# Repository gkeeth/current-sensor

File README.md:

# current-sensor
Hall effect current sensor board. Invasive (connected in series with DUT), with BNC output to oscilloscope.

Designed to fit in Hammond 1593W enclosure. Powered by 9V battery. Includes PCBs for front and back panels (20A and 36A options for front panel).

## Specifications:
- Output: 0-5V, DC-coupled
- Maximum input current: +/-20A. Different current limits are possible by
selecting a different version of the ACS730 Hall effect IC (also changes sensitivity)
  - ACS730xxxxx-20AB: +/- 20A
  - ACS730xxxxx-40AB: +/- 40A [limited to 36A by binding posts]
- Gain: selectable between x1, x10, and x100
  - -20AB: x1 (100mV/A), x10 (1V/A), and x100 (10V/A)
  - -40AB: x1 (50mV/A), x10 (500mV/A), and x100 (5V/A)
- Bandwidth: selectable between 1kHz, 10kHz, and 100kHz
- Power supply: 9V battery

## Adjustment Procedure:
The only adjustment needed is to adjust the zero-current offset voltage so that
the output reads zero when zero current is applied to the input.

1. Disconnect wires from input jacks so that input current is zero.
2. Set Gain to 1x and Bandwidth to 1kHz.
3. Adjust trimmer RV1 until the voltage at the output (between BNC center pin
and shell) is as close to 0V as possible.
4. Increase gain to 10x/100x and fine-tune adjustment.

## Possible Future Improvements:
- use a multi-turn trimpot for zero-current offset adjustment
- make adjustment trimpot available at rear panel for trim without removing case

## Schematic:
[PDF of schematic](pdf/current-sensor.pdf)

## Layout:

## BOM:
[BOM for main board](bom/current-sensor.csv)

### Additional components:
Note that the board was designed with Molex SL crimp terminals for the LED and 9V battery,
but those connections could be done with another crimp family or even soldered. Substitute
connectors as appropriate.

| Quantity | Manufacturer | Manufacturer PN  | Distributor | Distributor PN | Notes                |
| -------- | ------------ | ---------------- | ----------- | -------------- | -------------------- |
| 1        | Hammond      | 1593WBK          | Digikey     | 164-1593WBK-ND | case                 |
| 1        | Hammond      | 1593ATS50        | Digikey     | HM1442-ND      | PCB mounting screws  |
| 1        | MPD          | BH9VW            | Digikey     | BH9VW-ND       | battery holder       |
| 2        | Cal Test     | CT2232-4         | Digikey     | BKCT2232-4-ND  | binding posts        |
| 1        | C&K          | G003G            | Digikey     | 401-1205-ND    | power button cap     |
| 1        | Lumex        | SSI-LXH312ID-150 | Digikey     | 67-1190-ND     | power LED            |
| 2        | Molex        | 0190050010       | Digikey     | WM18241-ND     | QC connectors        |
| 4        | Molex        | 0016020097       | Digikey     | WM2513-ND      | SL crimp terminals for LED and battery |
| 2        | Molex        | 0050579402       | Digikey     | WM2900-ND      | SL crimp housings for LED and battery  |

## Front/Rear Panel and Assembly:

## License:
Licensed under the [Creative Commons Attribution-ShareAlike 4.0 International License][cc-by-sa].

[![CC BY-SA 4.0][cc-by-sa-image]][cc-by-sa]

[cc-by-sa]: http://creativecommons.org/licenses/by-sa/4.0/
[cc-by-sa-image]: https://licensebuttons.net/l/by-sa/4.0/88x31.png

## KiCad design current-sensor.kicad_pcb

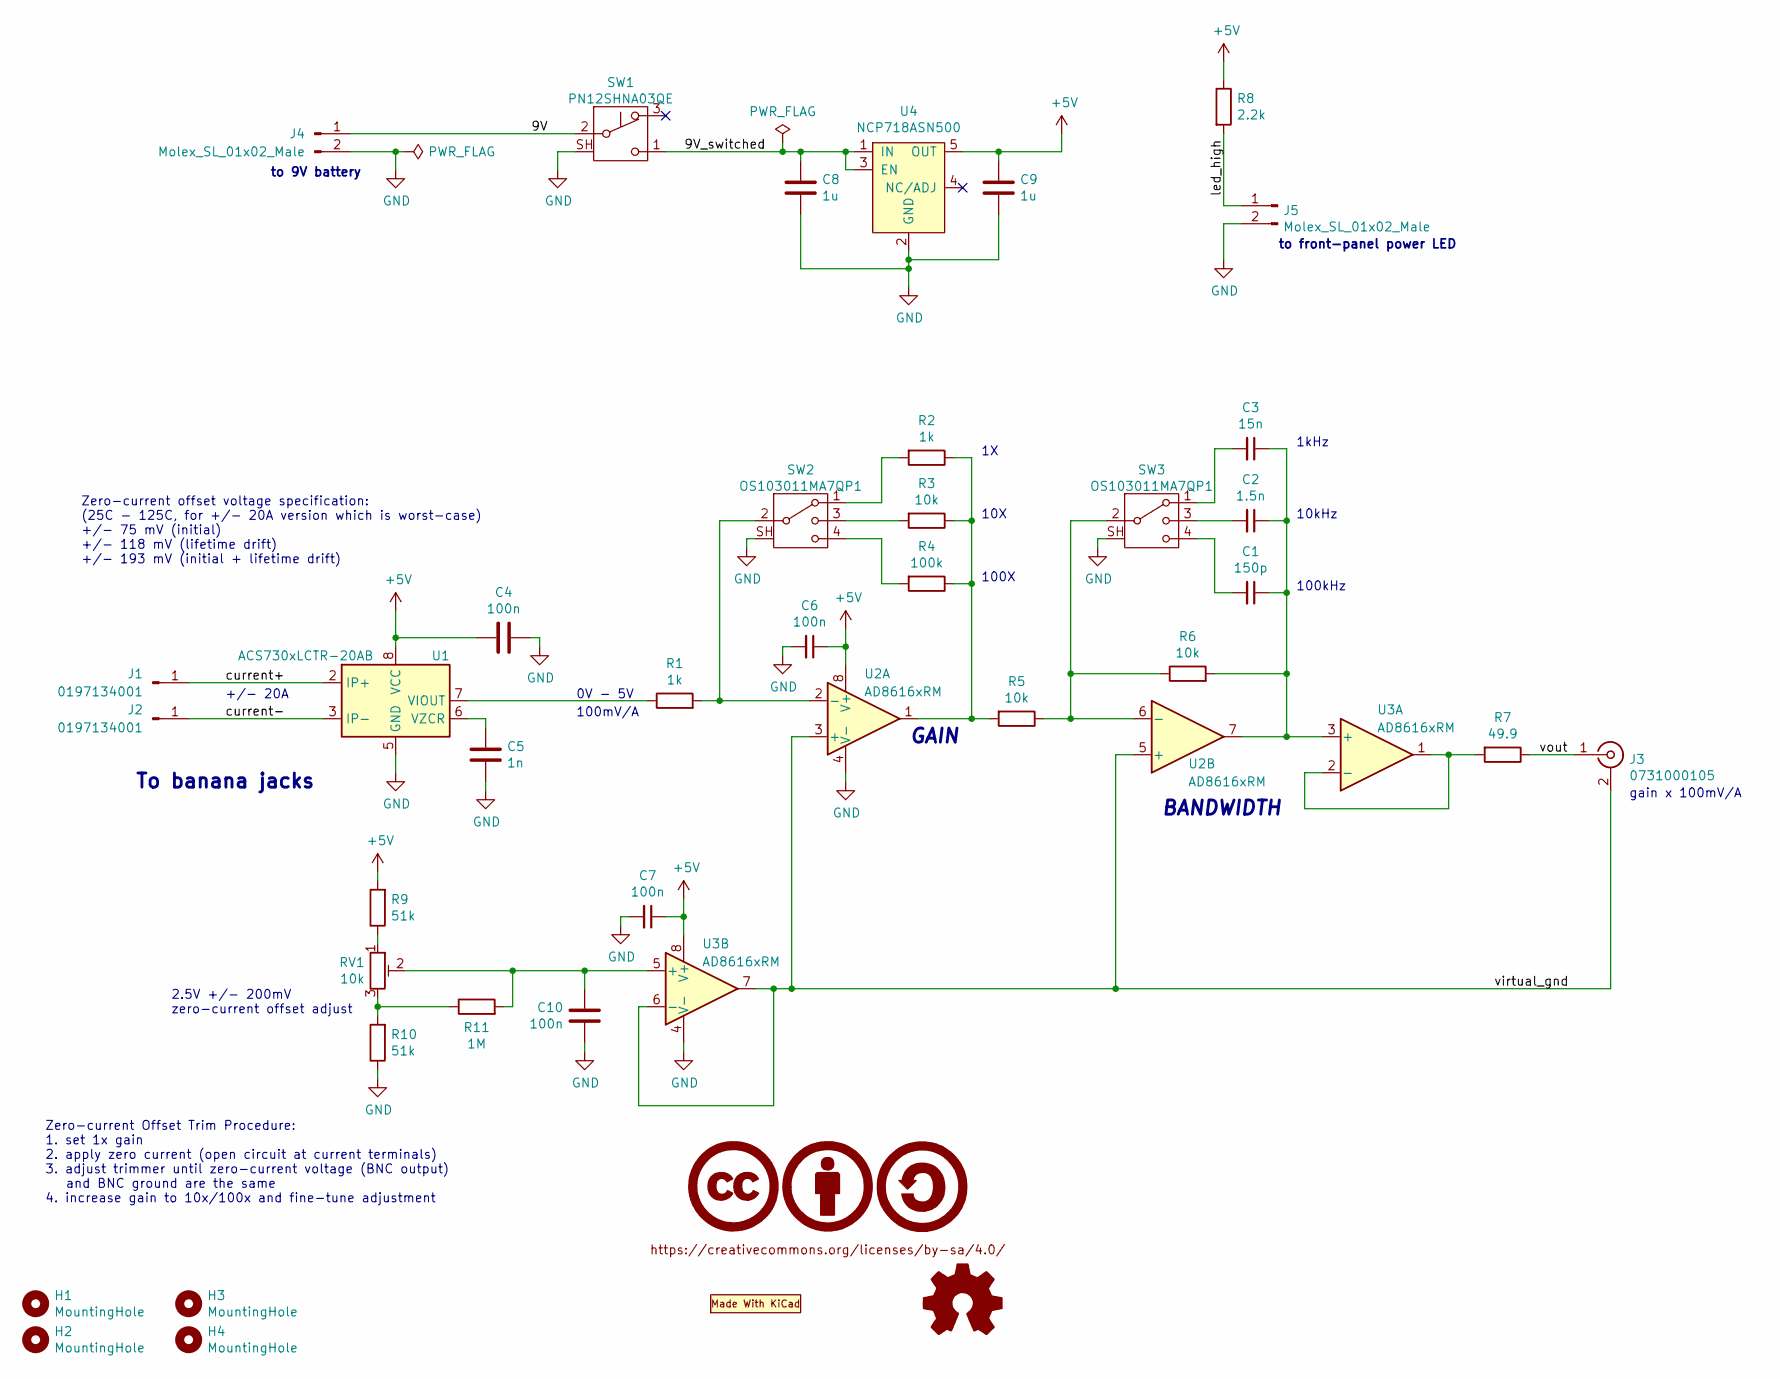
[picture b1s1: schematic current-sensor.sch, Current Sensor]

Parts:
C1: 150p; C_0603_1608Metric
C2: 1.5n; C_0603_1608Metric
C3: 15n; C_0603_1608Metric
C4, C6, C7, C10: 100n; C_0603_1608Metric
C5: 1n; C_0603_1608Metric
C8, C9: 1u; C_0805_2012Metric
H1, H2, H3, H4: MountingHole; MountingHole_3.2mm_M3
J1, J2: ‎0197134001‎; Connector_Molex_Quixon_19713-4001_1x01_Horizontal; Manufacturer PN 0197134001
J3: 0731000105; BNC_Molex_73100-0105_Horizontal; Manufacturer PN 0731000105
J4, J5: Molex_SL_01x02_Male; Molex_SL_A-70543-0001_1x02_P2.54mm_Vertical; Manufacturer PN 0705430001
LOGO1: CC-BY-SA_0.5in; CC-BY-SA_SilkScreenTop_Small
LOGO2: Logo_MadeWithKiCad; KiCad-Logo2_6mm_SilkScreen
LOGO3: Logo_Open_Hardware_Small; OSHW-Logo2_7.3x6mm_SilkScreen
R1, R2: 1k; R_0603_1608Metric
R3, R5, R6: 10k; R_0603_1608Metric
R4: 100k; R_0603_1608Metric
R7: 49.9; R_0603_1608Metric
R8: 2.2k; R_0603_1608Metric
R9, R10: 51k; R_0603_1608Metric
R11: 1M; R_0603_1608Metric
RV1: 10k; Potentiometer_Vishay_TS53YL_Vertical; Manufacturer PN TS53YL103MR10
SW1: PN12SHNA03QE; SW_Push_SPDT_CK_PN1xSxxx03QE; Manufacturer PN PN12SHNA03QE
SW2, SW3: OS103011MA7QP1; SW_Slide_SP3T_CK_OS103011MA7QP1; Manufacturer PN OS103011MA7QP1
U1: ACS730xLCTR-20AB; SOIC-8_3.9x4.9mm_P1.27mm; Manufacturer PN ACS730KLCTR-20AB-T
U2, U3: AD8616xRM; SOIC-8_3.9x4.9mm_P1.27mm; Manufacturer PN AD8616ARZ-REEL7
U4: NCP718ASN500; TSOT-23-5; Manufacturer PN NCP718ASN500T1G

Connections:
+5V: C4.2, C6.1, C7.1, C9.1, R8.1, R9.2, U1.8 (VCC), U2.8 (V+), U3.8 (V+), U4.5 (OUT)
/9V: J4.1, SW1.2 (B)
/9V_switched: C8.1, SW1.1 (C), U4.1 (IN), U4.3 (EN)
/current+: J1.1, U1.1 (IP+), U1.2 (IP+)
/current-: J2.1, U1.3 (IP-), U1.4 (IP-)
/led_high: J5.1, R8.2
/virtual_gnd: J3.2 (Ext), U2.3 (+), U2.5 (+), U3.6 (-), U3.7
/vout: J3.1 (In), R7.1
GND: C4.1, C5.2, C6.2, C7.2, C8.2, C9.2, C10.2, J4.2, J5.2, R10.1, SW1.SH, SW2.SH, SW3.SH, U1.5 (GND), U2.4 (V-), U3.4 (V-), U4.2 (GND)
unnamed: C1.1, C2.1, C3.1, R6.2, U2.7, U3.3 (+)
unnamed: C1.2, SW3.4
unnamed: C2.2, SW3.3
unnamed: C3.2, SW3.1
unnamed: C5.1, U1.6 (VZCR)
unnamed: C10.1, R11.2, RV1.2, U3.5 (+)
unnamed: R1.1, U1.7 (VIOUT)
unnamed: R1.2, SW2.2, U2.2 (-)
unnamed: R2.1, R3.1, R4.1, R5.2, U2.1
unnamed: R2.2, SW2.1
unnamed: R3.2, SW2.3
unnamed: R4.2, SW2.4
unnamed: R5.1, R6.1, SW3.2, U2.6 (-)
unnamed: R7.2, U3.1, U3.2 (-)
unnamed: R9.1, RV1.1
unnamed: R10.2, R11.1, RV1.3

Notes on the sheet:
0V - 5V
10X
100X
100kHz
10kHz
1kHz
To banana jacks
GAIN
BANDWIDTH
to front-panel power LED
to 9V battery
100mV/A
+/- 20A
gain x 100mV/A
Zero-current Offset Trim Procedure: 1. set 1x gain 2. apply zero current (open circuit at current terminals) 3. adjust trimmer until zero-current voltage (BNC output) and BNC ground are the same 4. increase gain to 10x/100x and fine-tune adjustment
2.5V +/- 200mV zero-current offset adjust
Zero-current offset voltage specification: (25C - 125C, for +/- 20A version which is worst-case) +/- 75 mV (initial) +/- 118 mV (lifetime drift) +/- 193 mV (initial + lifetime drift)

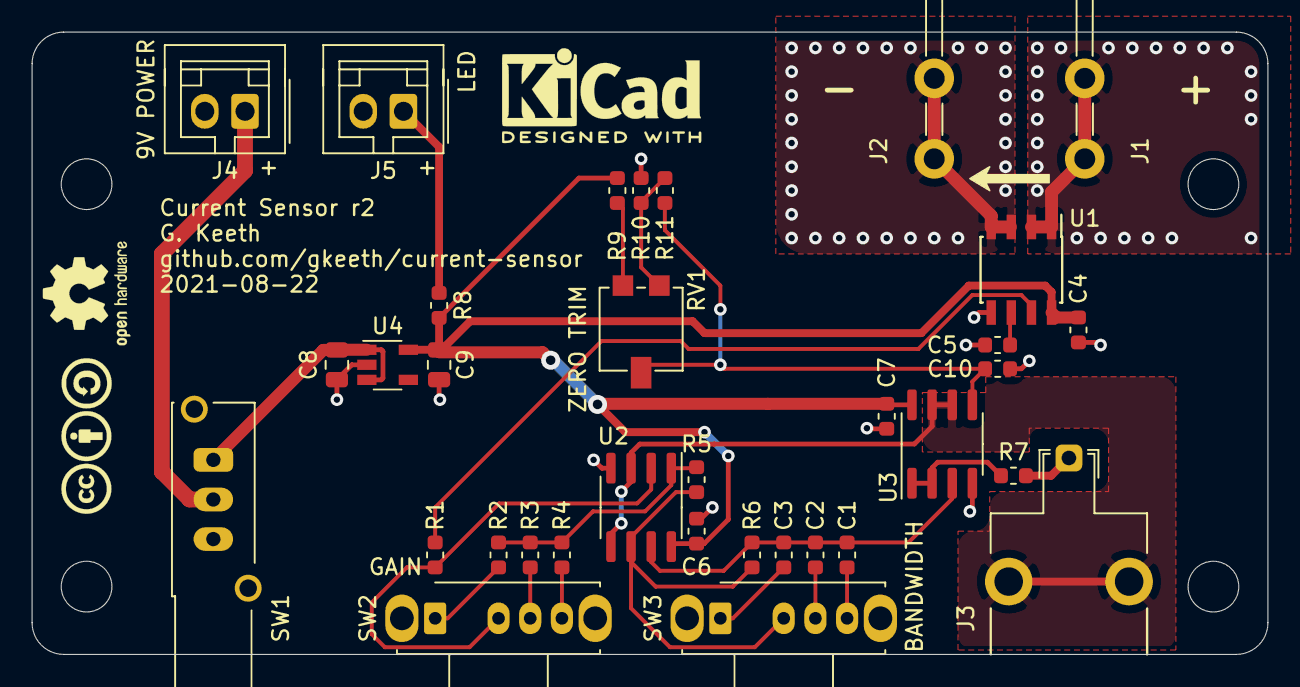
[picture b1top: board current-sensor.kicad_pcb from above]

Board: 2 copper layers, 78.0 x 39.3 mm, 41 parts (0 on the bottom side), 25 nets.

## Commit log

2020-06-30 add license
2020-06-30 fix license info in README
2020-06-30 add gitignore
2020-07-01 initial schematic design
2020-07-02 fix opamp power unit annotation
2020-08-04 mostly complete schematic and initial placement
2020-08-07 add mechanical models for enclosure, battery holder, and binding posts
2020-08-09 update 3d models in main board
2020-08-09 add pcb project for back panel
2020-08-09 Add mechanical 3d models
    all 3d models added are licensed identically to the rest of the project
    (CC-BY-SA). Manufacturer 3d models are not tracked in the repository
    because they are restrictively licensed.
2020-08-09 ignore all manufacturer 3d models & derivatives
2020-08-09 update paths for 3d models
2020-08-10 ignore a freecad backup file
2020-08-14 complete mechanical placement of all components on main pcb, and holes on front/back panels
2020-08-14 update README with enclosure details
2020-08-22 specify Hammond in readme
2020-08-25 complete basic schematic & routing
2020-08-25 thicken traces
2020-08-25 remove note about #4 clearance hole size
2020-08-25 update titleblocks
2020-08-25 add images to README
2020-08-25 add power flag to GND and add PDF schematic
2020-08-25 update README with specs & details
2020-08-25 README formatting
2020-08-25 fix header formatting
2020-08-25 add battery details to readme
2020-08-25 pcb churn from plotting
2020-10-18 swap 100kHz and 1kHz bandwidth positions
2020-10-18 Change hall effect sensor to +/-20A
    binding posts are limited to 15A. Decrease hall effect sensor range to
    lowest available (+/-20A).
    It is possible to use the equivalent part with a higher current range,
    but the connectors would need to be modified and the overall system gain
    would decrease due to reduced sensor sensitivity.
2020-10-18 update pcb with hall effect sensor PN change
2020-10-18 add draft svgs for front panel
2020-10-18 add switch mockup and update silk lines
2020-10-21 complete initial design of frontpanel.svg, before converting strokes to paths
2020-10-23 complete front panel label
2020-10-26 update svg makefile for multiple sources
2020-10-26 add draft back panel label; missing current arrow
2020-10-26 add back panel label
2020-10-26 adjust planes around current connectors and add silk
2020-10-26 update specs in README
2020-10-27 move frontpanel to correct origin
2020-10-27 redraw arrow on back panel
2020-10-27 increase svg2mod precision
2020-10-27 add name of instrument to front panel
2020-10-27 add 36A version of frontpanel footprint
2020-10-27 update text on backpanel to 36A Max (binding post limit)
2020-10-29 fix text on 36A frontpanel
2020-10-29 update backpanel footprint
2020-10-29 generate gerbers for backpanel
2020-10-29 generate gerbers for 36A and 20A frontpanel
2020-10-30 decrease solder mask clearance to 0 as recommended
2020-10-30 add JLC order number silk
2020-10-30 add JLC order number text to backpanel
2020-10-30 update backpanel gerbers with JLC order number text
2020-10-30 add gerbers for main pcb
2020-11-10 add fab/silk polarity marks to led/power connectors
2020-11-10 add interactive HTML bom
2020-11-10 label power/LED connectors
2020-11-10 update ibom with connector labels
2020-11-10 fix C8 silk position
2020-12-08 revision 1 of current sensor
    - fix gain/bandwidth switch pin numbering
    - move faston connectors further apart
    - switch from MSOP to SOIC package for op-amp
    - add silk labels to switches and connectors
    - reduce LED resistor to increase brightness
2020-12-14 update gerbers for rev1 main pcb
2020-12-14 update schematic plots, renders, and readme
2020-12-14 add sections to readme
2020-12-14 ignore gerber zips
2020-12-14 upate ibom for rev1
2020-12-14 add ordering info to schematic
2020-12-14 add bom
2020-12-16 add BOM to readme
2020-12-16 fix headings in README
2020-12-16 remove duplicated led in BOM
2021-01-03 don't ignore csv files
2021-01-04 add zero-current offset trim
2021-08-23 Change offset trim circuit
    completely ignore reference output from current sensor IC. Instead, use
    trimpot to get 2.5V +/- 200mV reference voltage.
2021-08-23 generate gerbers for r2
2021-08-23 regenerate schematic/layout svg/pdf/png plots
2021-08-23 update bom for r2
2021-08-29 update ibom to r2
2021-12-05 Update README
    - remove WIP notice -- this is more or less finished.
    - add adjustment procedure to README
    - add ideas for future improvements to README
